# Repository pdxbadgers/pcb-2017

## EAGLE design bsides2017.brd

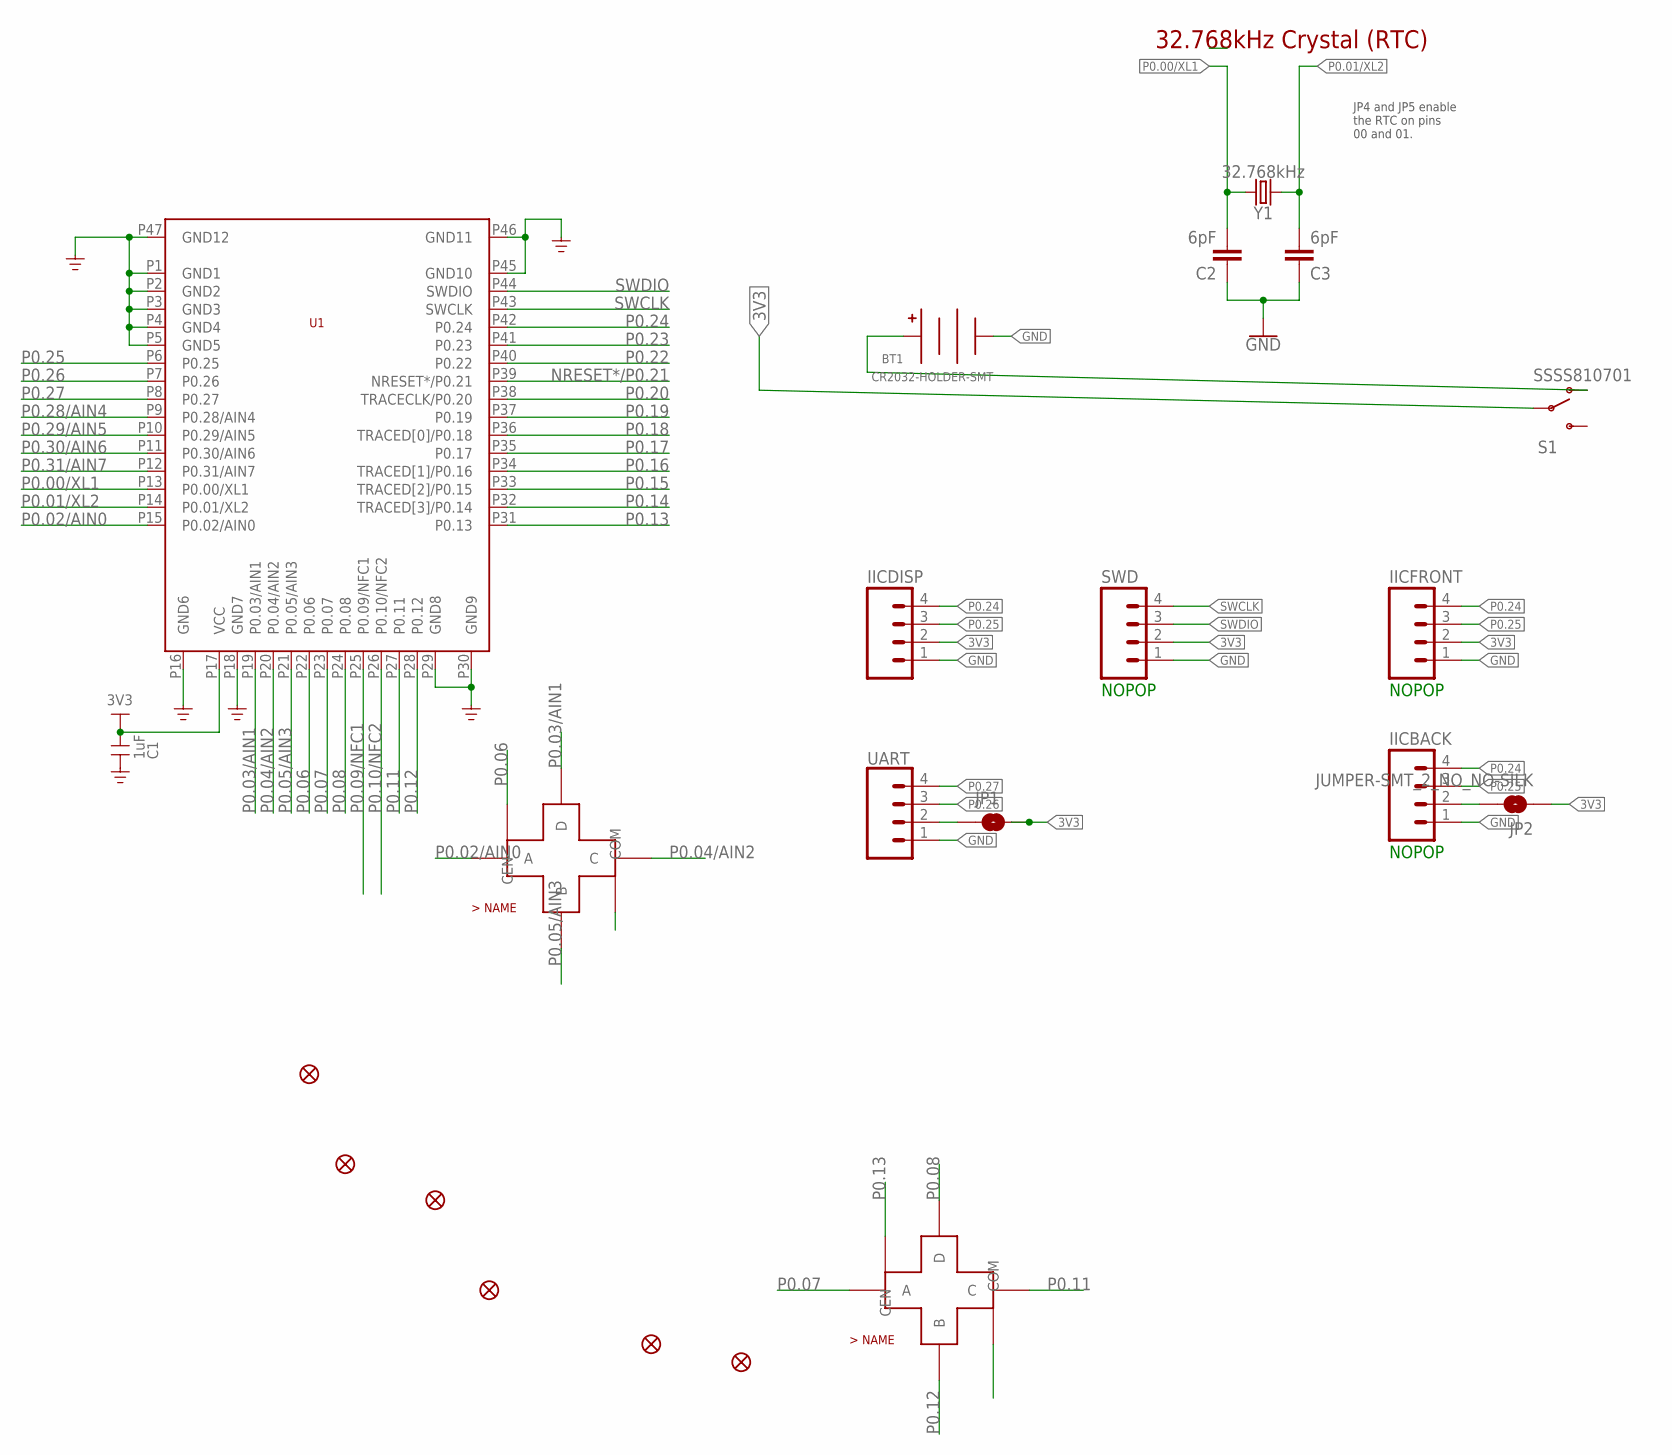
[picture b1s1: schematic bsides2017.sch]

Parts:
BT1: CR2032-HOLDER-SMT; S8211-46R
C1: 1uF; SMD0603
C2, C3: 6pF; 0402
FID1, FID2, FID3, FID4, FID5, FID6: FIDUCIAL1X2; FIDUCIAL-1X2
IICBACK: M04LOCK; 1X04_LOCK@1
IICDISP: M04LOCK; 1X04_LOCK@1
IICFRONT: M04LOCK; 1X04_LOCK@1
JP1, JP2: JUMPER-SMT_2_NO_NO-SILK; SMT-JUMPER_2_NO_NO-SILK
S1: SSSS810701; SSSS8
SWD: M04LOCK; 1X04_LOCK@1
U1: BMD-300
U$6, U$7: SKRHABE010
UART: CONN_04SMD; 1X04_SMD_RA_MALE
Y1: 32.768kHz; CRYSTAL-SMD-3.2X1.5MM

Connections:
3V3: C1.2 (3), IICDISP.2, IICFRONT.2, JP1.2, JP2.1, S1.P$2, SWD.2, U1.P17 (VCC)
GND: BT1.NEG, C1.1, C2.1, C3.1, IICBACK.1, IICDISP.1, IICFRONT.1, SWD.1, U1.P1 (GND1), U1.P2 (GND2), U1.P3 (GND3), U1.P4 (GND4), U1.P5 (GND5), U1.P16 (GND6), U1.P18 (GND7), U1.P29 (GND8), U1.P30 (GND9), U1.P45 (GND10), U1.P46 (GND11), U1.P47 (GND12), U$6.P$5 (COM), U$6.P$7 (COM), U$6.P$8 (COM), U$7.P$5 (COM), U$7.P$7 (COM), U$7.P$8 (COM), UART.1
unnamed: IICBACK.2, JP2.2
unnamed: BT1.POS0 (POS), BT1.POS1 (POS), S1.P$3 (O)
unnamed: JP1.1, UART.2
NRESET*/P0.21: U1.P39 (NRESET*/P0.21)
P0.00/XL1: C2.2, U1.P13 (P0.00/XL1), Y1.P$2 (2)
P0.01/XL2: C3.2, U1.P14 (P0.01/XL2), Y1.P$1 (1)
P0.02/AIN0: U1.P15 (P0.02/AIN0), U$6.P$1 (A)
P0.03/AIN1: U1.P19 (P0.03/AIN1), U$6.P$6 (D)
P0.04/AIN2: U1.P20 (P0.04/AIN2), U$6.P$3 (C)
P0.05/AIN3: U1.P21 (P0.05/AIN3), U$6.P$4 (B)
P0.06: U1.P22 (P0.06), U$6.P$2 (CEN)
P0.07: U1.P23 (P0.07), U$7.P$1 (A)
P0.08: U1.P24 (P0.08), U$7.P$6 (D)
P0.09/NFC1: U1.P25 (P0.09/NFC1)
P0.10/NFC2: U1.P26 (P0.10/NFC2)
P0.11: U1.P27 (P0.11), U$7.P$3 (C)
P0.12: U1.P28 (P0.12), U$7.P$4 (B)
P0.13: U1.P31 (P0.13), U$7.P$2 (CEN)
P0.14: U1.P32 (TRACED[3]/P0.14)
P0.15: U1.P33 (TRACED[2]/P0.15)
P0.16: U1.P34 (TRACED[1]/P0.16)
P0.17: U1.P35 (P0.17)
P0.18: U1.P36 (TRACED[0]/P0.18)
P0.19: U1.P37 (P0.19)
P0.20: U1.P38 (TRACECLK/P0.20)
P0.22: U1.P40 (P0.22)
P0.23: U1.P41 (P0.23)
P0.24: IICBACK.4, IICDISP.4, IICFRONT.4, U1.P42 (P0.24)
P0.25: IICBACK.3, IICDISP.3, IICFRONT.3, U1.P6 (P0.25)
P0.26: U1.P7 (P0.26), UART.3
P0.27: U1.P8 (P0.27), UART.4
P0.28/AIN4: U1.P9 (P0.28/AIN4)
P0.29/AIN5: U1.P10 (P0.29/AIN5)
P0.30/AIN6: U1.P11 (P0.30/AIN6)
P0.31/AIN7: U1.P12 (P0.31/AIN7)
SWCLK: SWD.4, U1.P43 (SWCLK)
SWDIO: SWD.3, U1.P44 (SWDIO)

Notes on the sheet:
32.768kHz Crystal (RTC)
JP4 and JP5 enable the RTC on pins 00 and 01.
NOPOP

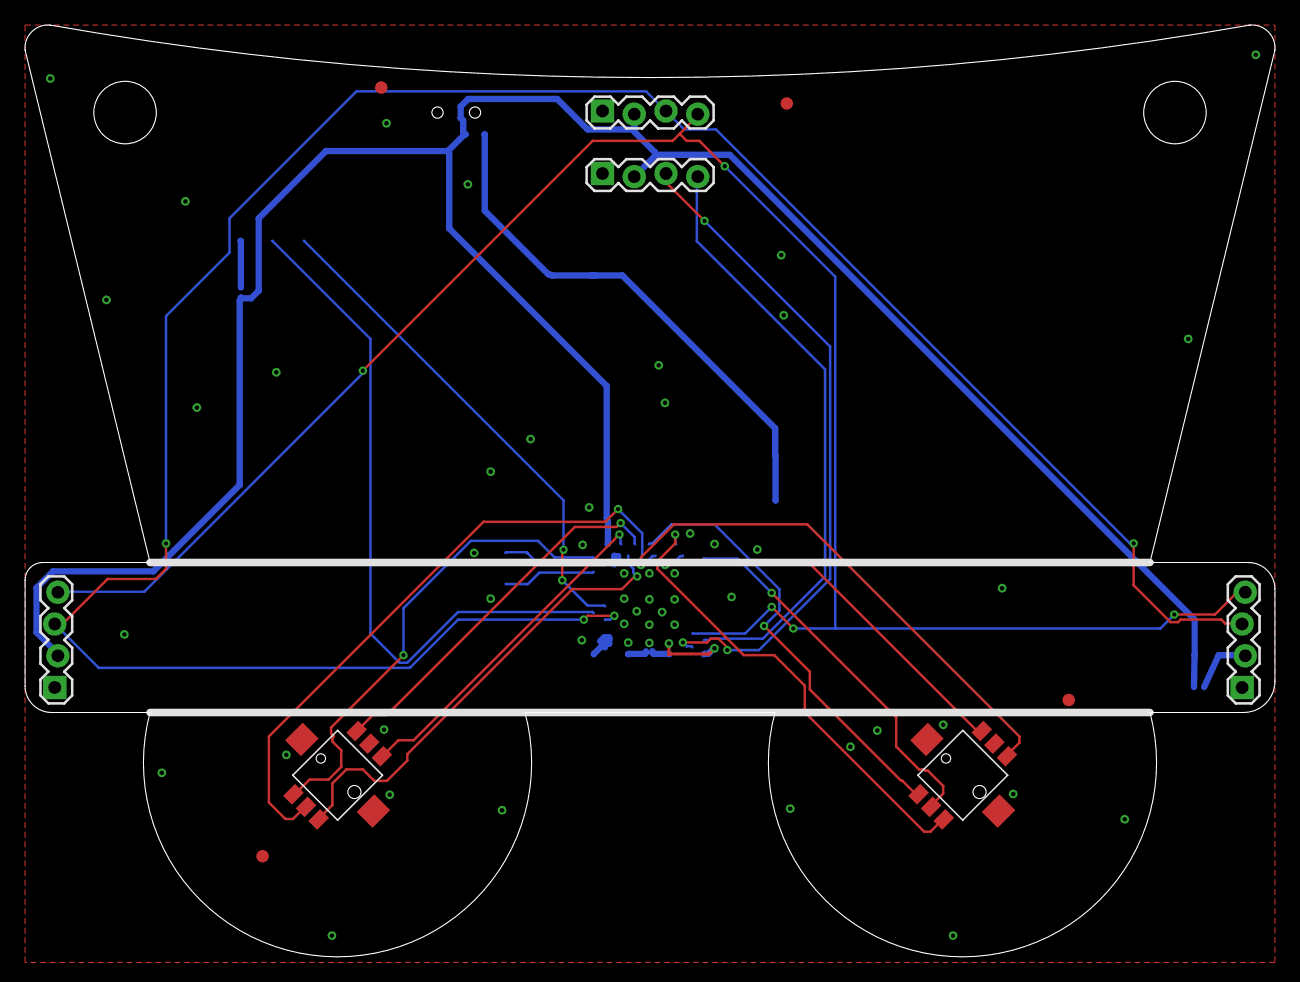
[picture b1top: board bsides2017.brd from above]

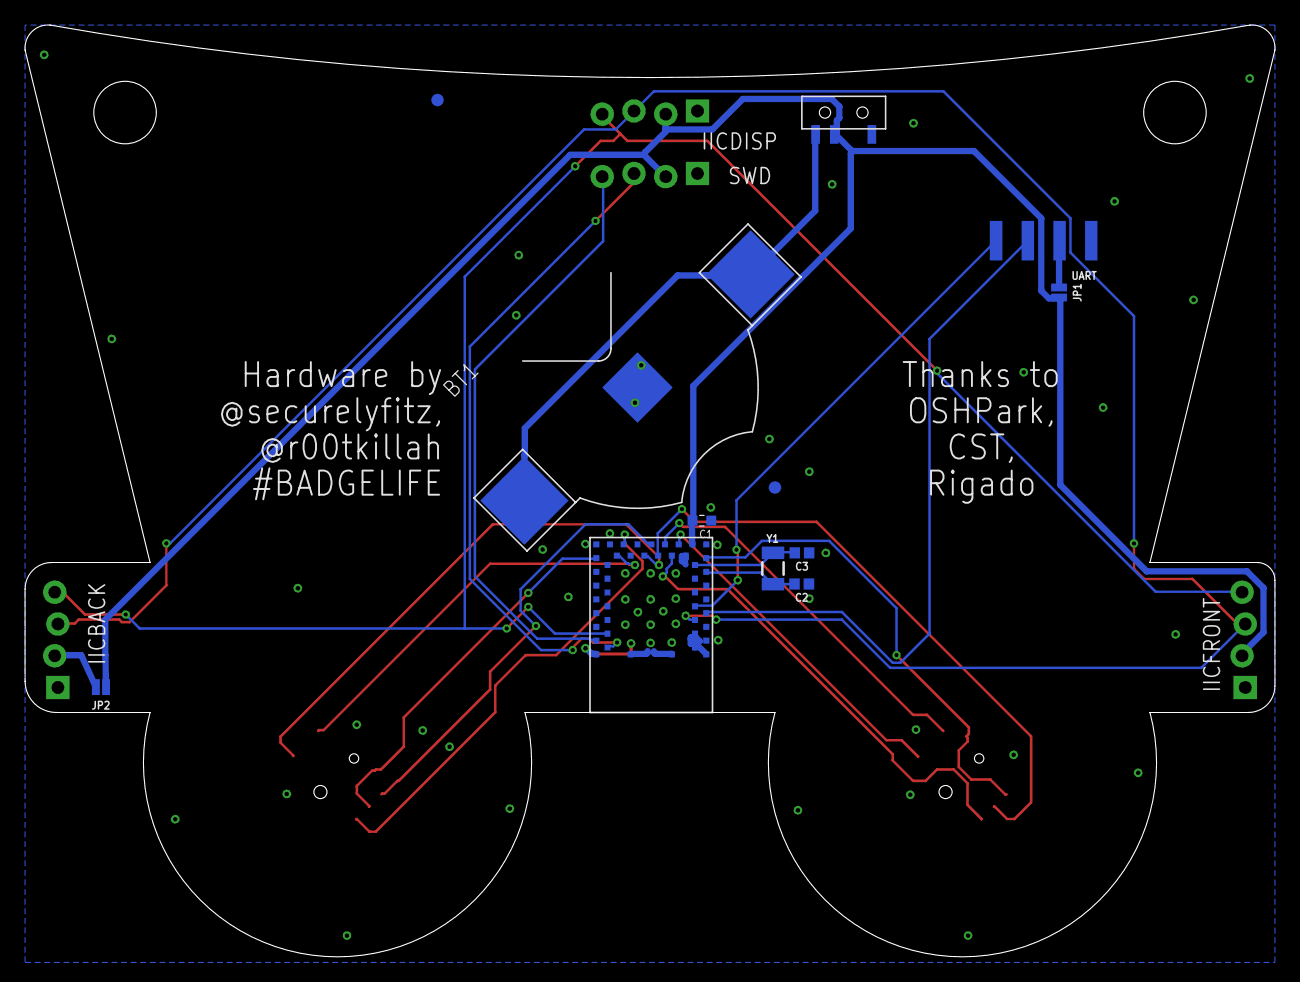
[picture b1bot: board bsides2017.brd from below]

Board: 2 copper layers, 100.0 x 74.6 mm, 22 parts (12 on the bottom side), 23 nets.

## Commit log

2017-10-21 badgers!!!

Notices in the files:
parts and their libraries:
SparkFun-Capacitors: Licensing: Creative Commons ShareAlike 4.0 International - https://creativecommons.org/licenses/by-sa/4.0
